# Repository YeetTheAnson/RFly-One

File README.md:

# RFly One

## Introduction
This project was inspired by [adsbee](https://github.com/PantsForBirds/adsbee) and [SoftRF](https://github.com/PantsForBirds/adsbee)!

This is the RFly One! This project was designed to be a fully offline general aviation proximity awareness system. The RFly One includes a custom ADS-B 1090MHz receiver frontend and support for FLARM AIR V7, OGNTP, FANET+ and more protocols, designed to keep pilots or enthusiasts aware of nearby manned or unmanned aerial vehicles without relying on an active internet connection.

The RFly One has a 2.4" TFT display to show nearby air traffic on an offline map (which can be loaded onto the SD card) or used as a flight insturment dashboard. It also has a BMI270 IMU and a MMC5983MA magnetometer to provide accurate heading, combined with an ATGM332D-5N31 GNSS module to show the current location on a map.

## Specifications

### Features
* **Awareness Protocols:** ADS-B, FLARM AIR V7, OGNTP, FANET+, RemoteID
* **Positioning:** GNSS, Gyro, Accelerometer, Magnetometer
* **Storage:** MicroSD Card (For offline maps and flight logging)
* **Charging:** 2A Max

### Hardware
* **Main Processor** ESP32-S3
* **ADS-B Decoder:** RP2040
* **Button/Power Control:** CH32V003
* **GNSS:** ATGM332D-5N31
* **IMU:** BMI270
* **Magnetometer:** MMC5983MA
* **LoRa Radio:** E80-900M2212S (LR2021)
* **Display:** 2.4" TFT

## Pinout
| Feature | Pin name | ESP32 Pin | Description |
|---|---|---|---|
| **LCD** | `LCD_MOSI` | `GPIO 42` | SPI MOSI |
| | `LCD_MISO` | `GPIO 39` | SPI MISO |
| | `LCD_SCK` | `GPIO 41` | SPI Clock |
| | `LCD_CS` | `GPIO 44` | SPI Chip Select |
| | `LCD_LED` | `GPIO 40` | Backlight Control |
| | `LCD_CMD` | `GPIO 43` | LCD Command |
| **IMU** | `SDA` | `GPIO 36` | I2C Data |
| | `SCL` | `GPIO 35` | I2C Clock |
| **SD Card** | `SDIO_DAT0` | `GPIO 9` | Data 0 |
| | `SDIO_DAT1` | `GPIO 8` | Data 1 |
| | `SDIO_DAT2` | `GPIO 12` | Data 2 |
| | `SDIO_DAT3` | `GPIO 13` | Data 3 |
| | `SDIO_CMD` | `GPIO 11` | SD Command |
| | `SDIO_CD` | `GPIO 7` | SD Detect |
| | `SDIO_CLK` | `GPIO 10` | SD Clock |
| **LoRa Radio** | `LORA_MOSI` | `GPIO 2` | SPI MOSI |
| | `LORA_MISO` | `GPIO 1` | SPI MISO |
| | `LORA_SCK` | `GPIO 4` | SPI Clock |
| | `LORA_CE` | `GPIO 5` | SPI Chip Enable |
| | `LORA_BUSY` | `GPIO 16` | Radio Busy |
| **GNSS Module** | `GNSS_TX` | `GPIO 15` | UART RX |
| | `GNSS_RX` | `GPIO 14` | UART TX |
| | `PPS` | `GPIO 17` | GNSS Time |
| **Button/Power Control** | `CH32_TX` | `GPIO 21` | UART RX |
| | `CH32_RX` | `GPIO 18` | UART TX |
| | `BATT_ADC` | `GPIO 6` | ADC1 |
| **ADSB Decoder** | `RP_TX` | `GPIO 47` | UART RX |
| | `RP_RX` | `GPIO 48` | UART TX |
| | `ADSB_CLK` | `GPIO 34` | Extracted Clock From ADSB Signal |

----

## Hardware Overview

----

## Firmware

### Building the RP2040 Firmware
1. Clone [this repository](https://github.com/YeetTheAnson/RFly-One) and enter the directory `cd RFly-One`
2. Open the `/firmware/source/rp2040.ino` file in ArduinoIDE
3. Paste `https://github.com/earlephilhower/arduino-pico/releases/download/global/package_rp2040_index.json` into `File > Preferences > Additional boards manager URLs`
4. Go to boards manager and install `Raspberry Pi Pico/RP2040/RP2350` by Earle F. Philhower, III
5. Click the upload button or `Sketch > Export Compiled Binary`

### Building the CH32V003 Firmware
1. Clone [this repository](https://github.com/YeetTheAnson/RFly-One) and enter the directory `cd RFly-One`
2. Open the `/firmware/source/ch32v003.ino` file in ArduinoIDE
3. Paste `https://alexandermandera.github.io/arduino-wch32v003/package_ch32v003_index.json` into `File > Preferences > Additional boards manager URLs`
4. Go to boards manager and install `WCH Boards` by Alexander Mandera
5. Click the upload button or `Sketch > Export Compiled Binary`

### Building the ESP32S3 Firmware
1. Clone [this repository](https://github.com/YeetTheAnson/RFly-One) and enter the directory `cd RFly-One`
2. Open the `/firmware/source/esp32.ino` file in ArduinoIDE
3. Paste `https://espressif.github.io/arduino-esp32/package_esp32_index.json` into `File > Preferences > Additional boards manager URLs`
4. Go to boards manager and install `ESP32` by Espressif
5. Click the upload button or `Sketch > Export Compiled Binary`

----

## Assembly

### Component List
* **Shell:**
    - [TopCase1.stl](https://github.com/YeetTheAnson/RFly-One/tree/main/production/3dPrint/TopCase1.stl)
    - [TopCase2.stl](https://github.com/YeetTheAnson/RFly-One/tree/main/production/3dPrint/TopCase2.stl)
    - [BottomCase.stl](https://github.com/YeetTheAnson/RFly-One/tree/main/production/3dPrint/BottomCase.stl)
* **PCB:**
    - [RFlyOne.zip](https://github.com/YeetTheAnson/RFly-One/tree/main/production/PCB/RFlyOne.zip)  
* **Fasteners:** 4x M2 10mm Self Tapping Screws
* **Battery:** Generic 500mAh LiPo battery (Size of battery is your choice)
* **SD Card:** Generic micro SD Card
* **Antennae:**
    - 2x 2400MHz FPC Antenna
    - 1x 1090MHz FPC Antenna
    - 1x 900MHz FPC Antenna
    - 1x Active GPS Ceramic Antenna

### Assembly Instructions
1. Slide the 3d printed parts `TopCase1.stl` and `TopCase2.stl` into place underneath the TFT LCD board.

2. Attach the battery using double sided adhesives and solder the battery cable onto the dedicated pad. Then connect the 2.4GHz WiFi antenna, 2.4GHz LoRa antenna, 1090MHz ADSB antenna and 900MHz LoRa antenna, and secure the FPC antennae to `BottomCase.stl` using double sided adhesives.

3. Feed the GNSS antenana cable through the `BottomCase.stl` cutout and glue the antenna to the bottom case. Then connect the GNSS antenna connector to the PCB and close the case.

4. Secure the case using 4x M2 10mm Self Tapping Screws

----

## Bill of Material

| Category | Item Name | Description | Link | Vendor | Quantity | Total Price (USD) |
|---|---|---|---|---|---:|---:|
| PCB Components | CL10A106MA8NRNC | 10uF 0603 capacitor | [link](https://www.lcsc.com/product-detail/C96446.html) | LCSC | 20 | 1.52 |
| PCB Components | AO3401A | P channel MOSFET | [link](https://www.lcsc.com/product-detail/C15127.html) | LCSC | 5 | 0.51 |
| PCB Components | GRM1555C1H101JA01D | 100pF 0402 capacitor | [link](https://www.lcsc.com/product-detail/C77177.html) | LCSC | 50 | 0.55 |
| PCB Components | GJM1555C1H3R0BB01D | 3pF 0402 capacitor | [link](https://www.lcsc.com/product-detail/C88891.html) | LCSC | 50 | 0.86 |
| PCB Components | CC0402JRNPO9BN201 | 200pF 0402 capacitor | [link](https://www.lcsc.com/product-detail/C325462.html) | LCSC | 50 | 0.45 |
| PCB Components | CC0402KRX7R9BB102 | 1nF 0402 capacitor | [link](https://www.lcsc.com/product-detail/C106205.html) | LCSC | 100 | 0.23 |
| PCB Components | CC0402JRNPO9BN150 | 15pF 0402 capacitor | [link](https://www.lcsc.com/product-detail/C106997.html) | LCSC | 100 | 0.20 |
| PCB Components | CL21A226MOQNNNE | 22uF 0805 capacitor | [link](https://www.lcsc.com/product-detail/C98190.html) | LCSC | 10 | 1.06 |
| PCB Components | RClamp3361P-ES | 0.25pF DFN1006 TVS diode | [link](https://www.lcsc.com/product-detail/C22464622.html) | LCSC | 5 | 0.60 |
| PCB Components | 0402L020/6SR | 200mA 0402 PTC Fuse | [link](https://www.lcsc.com/product-detail/C53280164.html) | LCSC | 10 | 0.71 |
| PCB Components | LQW15CN77NJ10D | 77nH 0402 inductor | [link](https://www.lcsc.com/product-detail/C668466.html) | LCSC | 10 | 0.88 |
| PCB Components | LQG15HS10NJ02D | 10nH 0402 inductor | [link](https://www.lcsc.com/product-detail/C77103.html) | LCSC | 50 | 0.93 |
| PCB Components | RC0402FR-0727RL | 27R 0402 resistor | [link](https://www.lcsc.com/product-detail/C138021.html) | LCSC | 100 | 0.40 |
| PCB Components | RC0402FR-0745K3L | 45.3k 0402 resistor | [link](https://www.lcsc.com/product-detail/C137977.html) | LCSC | 100 | 0.17 |
| PCB Components | FRC0402F2701TS | 2.7k 0402 resistor | [link](https://www.lcsc.com/product-detail/C2909332.html) | LCSC | 100 | 0.19 |
| PCB Components | FRC0402F1600TS | 160R 0402 resistor | [link](https://www.lcsc.com/product-detail/C2933075.html) | LCSC | 100 | 0.18 |
| PCB Components | FRC0402F3300TS | 330R 0402 resistor | [link](https://www.lcsc.com/product-detail/C2930002.html) | LCSC | 100 | 0.22 |
| PCB Components | FRC0402F7322TS | 73.2k 0402 resistor | [link](https://www.lcsc.com/product-detail/C2998163.html) | LCSC | 100 | 0.19 |
| PCB Components | 0402WGF7501TCE | 7.5k 0402 resistor | [link](https://www.lcsc.com/product-detail/C25918.html) | LCSC | 100 | 0.22 |
| PCB Components | ABM8-272-T3 | 12MHz 10pF 3225 crystal | [link](https://www.lcsc.com/product-detail/C20625731.html) | LCSC | 1 | 0.63 |
| PCB Components | ATGM332D-5N31 | GNSS module | [link](https://www.lcsc.com/product-detail/C128659.html) | LCSC | 1 | 3.58 |
| PCB Components | BMI270 | IMU | [link](https://www.lcsc.com/product-detail/C2836813.html) | LCSC | 2 | 5.75 |
| PCB Components | BQ25606RGER | Battery charge controller | [link](https://www.lcsc.com/product-detail/C374063.html) | LCSC | 1 | 1.64 |
| PCB Components | MMC5983MA | Magnetometer | [link](https://www.lcsc.com/product-detail/C404329.html) | LCSC | 1 | 2.28 |
| PCB Components | RT9193-33GB | 3.3V LDO regulator | [link](https://www.lcsc.com/product-detail/C15651.html) | LCSC | 5 | 0.69 |
| PCB Components | TA0970A | 1090MHz SAW filter | [link](https://www.lcsc.com/product-detail/C7115531.html) | LCSC | 2 | 3.09 |
| PCB Components | TLV3201AIDBVR | Comparator | [link](https://www.lcsc.com/product-detail/C105188.html) | LCSC | 1 | 0.98 |
| PCB Components | TPS61023DRLR | Boost converter | [link](https://www.lcsc.com/product-detail/C919459.html) | LCSC | 5 | 1.24 |
| PCB Components | TPS7A0230PDBVR | ULC 3V LDO regulator | [link](https://www.lcsc.com/product-detail/C3747031.html) | LCSC | 1 | 0.45 |
| PCB Components | TQP3M9036 | LNA | [link](https://www.lcsc.com/product-detail/C920261.html) | LCSC | 2 | 6.29 |
| PCB Components | TXU0202DTTR | Logic level translator | [link](https://www.lcsc.com/product-detail/C18197534.html) | LCSC | 2 | 1.62 |
| PCB Components | W25Q128JVSIQ | 128Mb 16MB NOR flash | [link](https://www.lcsc.com/product-detail/C97521.html) | LCSC | 1 | 2.58 |
| PCB Components | ESP32-S3-MINI-1U-N4R2 | Main processor | [link](https://www.lcsc.com/product-detail/C22356044.html) | LCSC | 1 | 4.61 |
| PCB Components | RP2040 | ADSB decoder coprocessor | [link](https://www.lcsc.com/product-detail/C2040.html) | LCSC | 1 | 1.00 |
| PCB Components | LCSC Shipping | 4PX | - | LCSC | 1 | 4.71 |
| PCB | PCB | 4 layer bare PCB | - | JLCPCB | 1 | 8.00 |
| PCB | JLCPCB Shipping | E-POST | - | JLCPCB | 1 | 5.78 |
| PCB Components | E80-900M2213S | LR2021 LoRA module | [link](https://www.aliexpress.com/item/1005012863308600.html) | AliExpress | 1 | 8.69 |
| PCB Components | AD8313ARMZ | RF logarithmic power detector | [link](https://www.aliexpress.com/item/1005009749065916.html) | AliExpress | 1 | 3.31 |
| PCB Components | AliExpress Shipping | AliExpress Shipping | - | AliExpress | 1 | 5.79 |
| Parts | 2.4" TFT LCD | 2.4" TFT LCD | [link](https://shopee.com.my/TFT-Display-0.96-1.3-1.44-1.77-1.8-2.4-2.8-inch-IPS-7P-SPI-HD-65K-TFT-Full-Color-LCD-Module-ST7735-Drive-IC-80*160-For-Arduino-i.299149454.21474104300) | Shopee | 1 | 4.35 |
| Parts | UWB 700-2700MHz antenna large | For 1090MHz ADSB receiver | [link](https://shopee.com.my/Gsm-3G-4G-LTE-5G-nb-iot-iot-Module-Signal-Enhancement-FPC-PCB-Built-in-Patch-Antenna-i.419312080.27871596372) | Shopee | 1 | 0.70 |
| Parts | UWB 700-2700MHz antenna small | For 900MHz LoRa transceiver | [link](https://shopee.com.my/Gsm-3G-4G-LTE-5G-nb-iot-iot-Module-Signal-Enhancement-FPC-PCB-Built-in-Patch-Antenna-i.419312080.27871596373) | Shopee | 1 | 0.65 |
| Parts | 2.4GHz antenna | For ESP32 WiFi/BT and LoRa | [link](https://shopee.com.my/2.4g-5g-5.8g-Dual-Band-Antenna-Built-in-FPC-Soft-Board-Antenna-wifi-Bluetooth-PCB-Patch-ipex-Antenna-i.419312080.27171149912) | Shopee | 2 | 0.95 |
| Parts | Shopee Shipping | SPX Express | - | Shopee | 2 | 2.60 |

- **PCB Components Total:** $69.00
- **PCB Total:** $13.78
- **Parts Total:** $9.25
### **Grand Total:** $92.03

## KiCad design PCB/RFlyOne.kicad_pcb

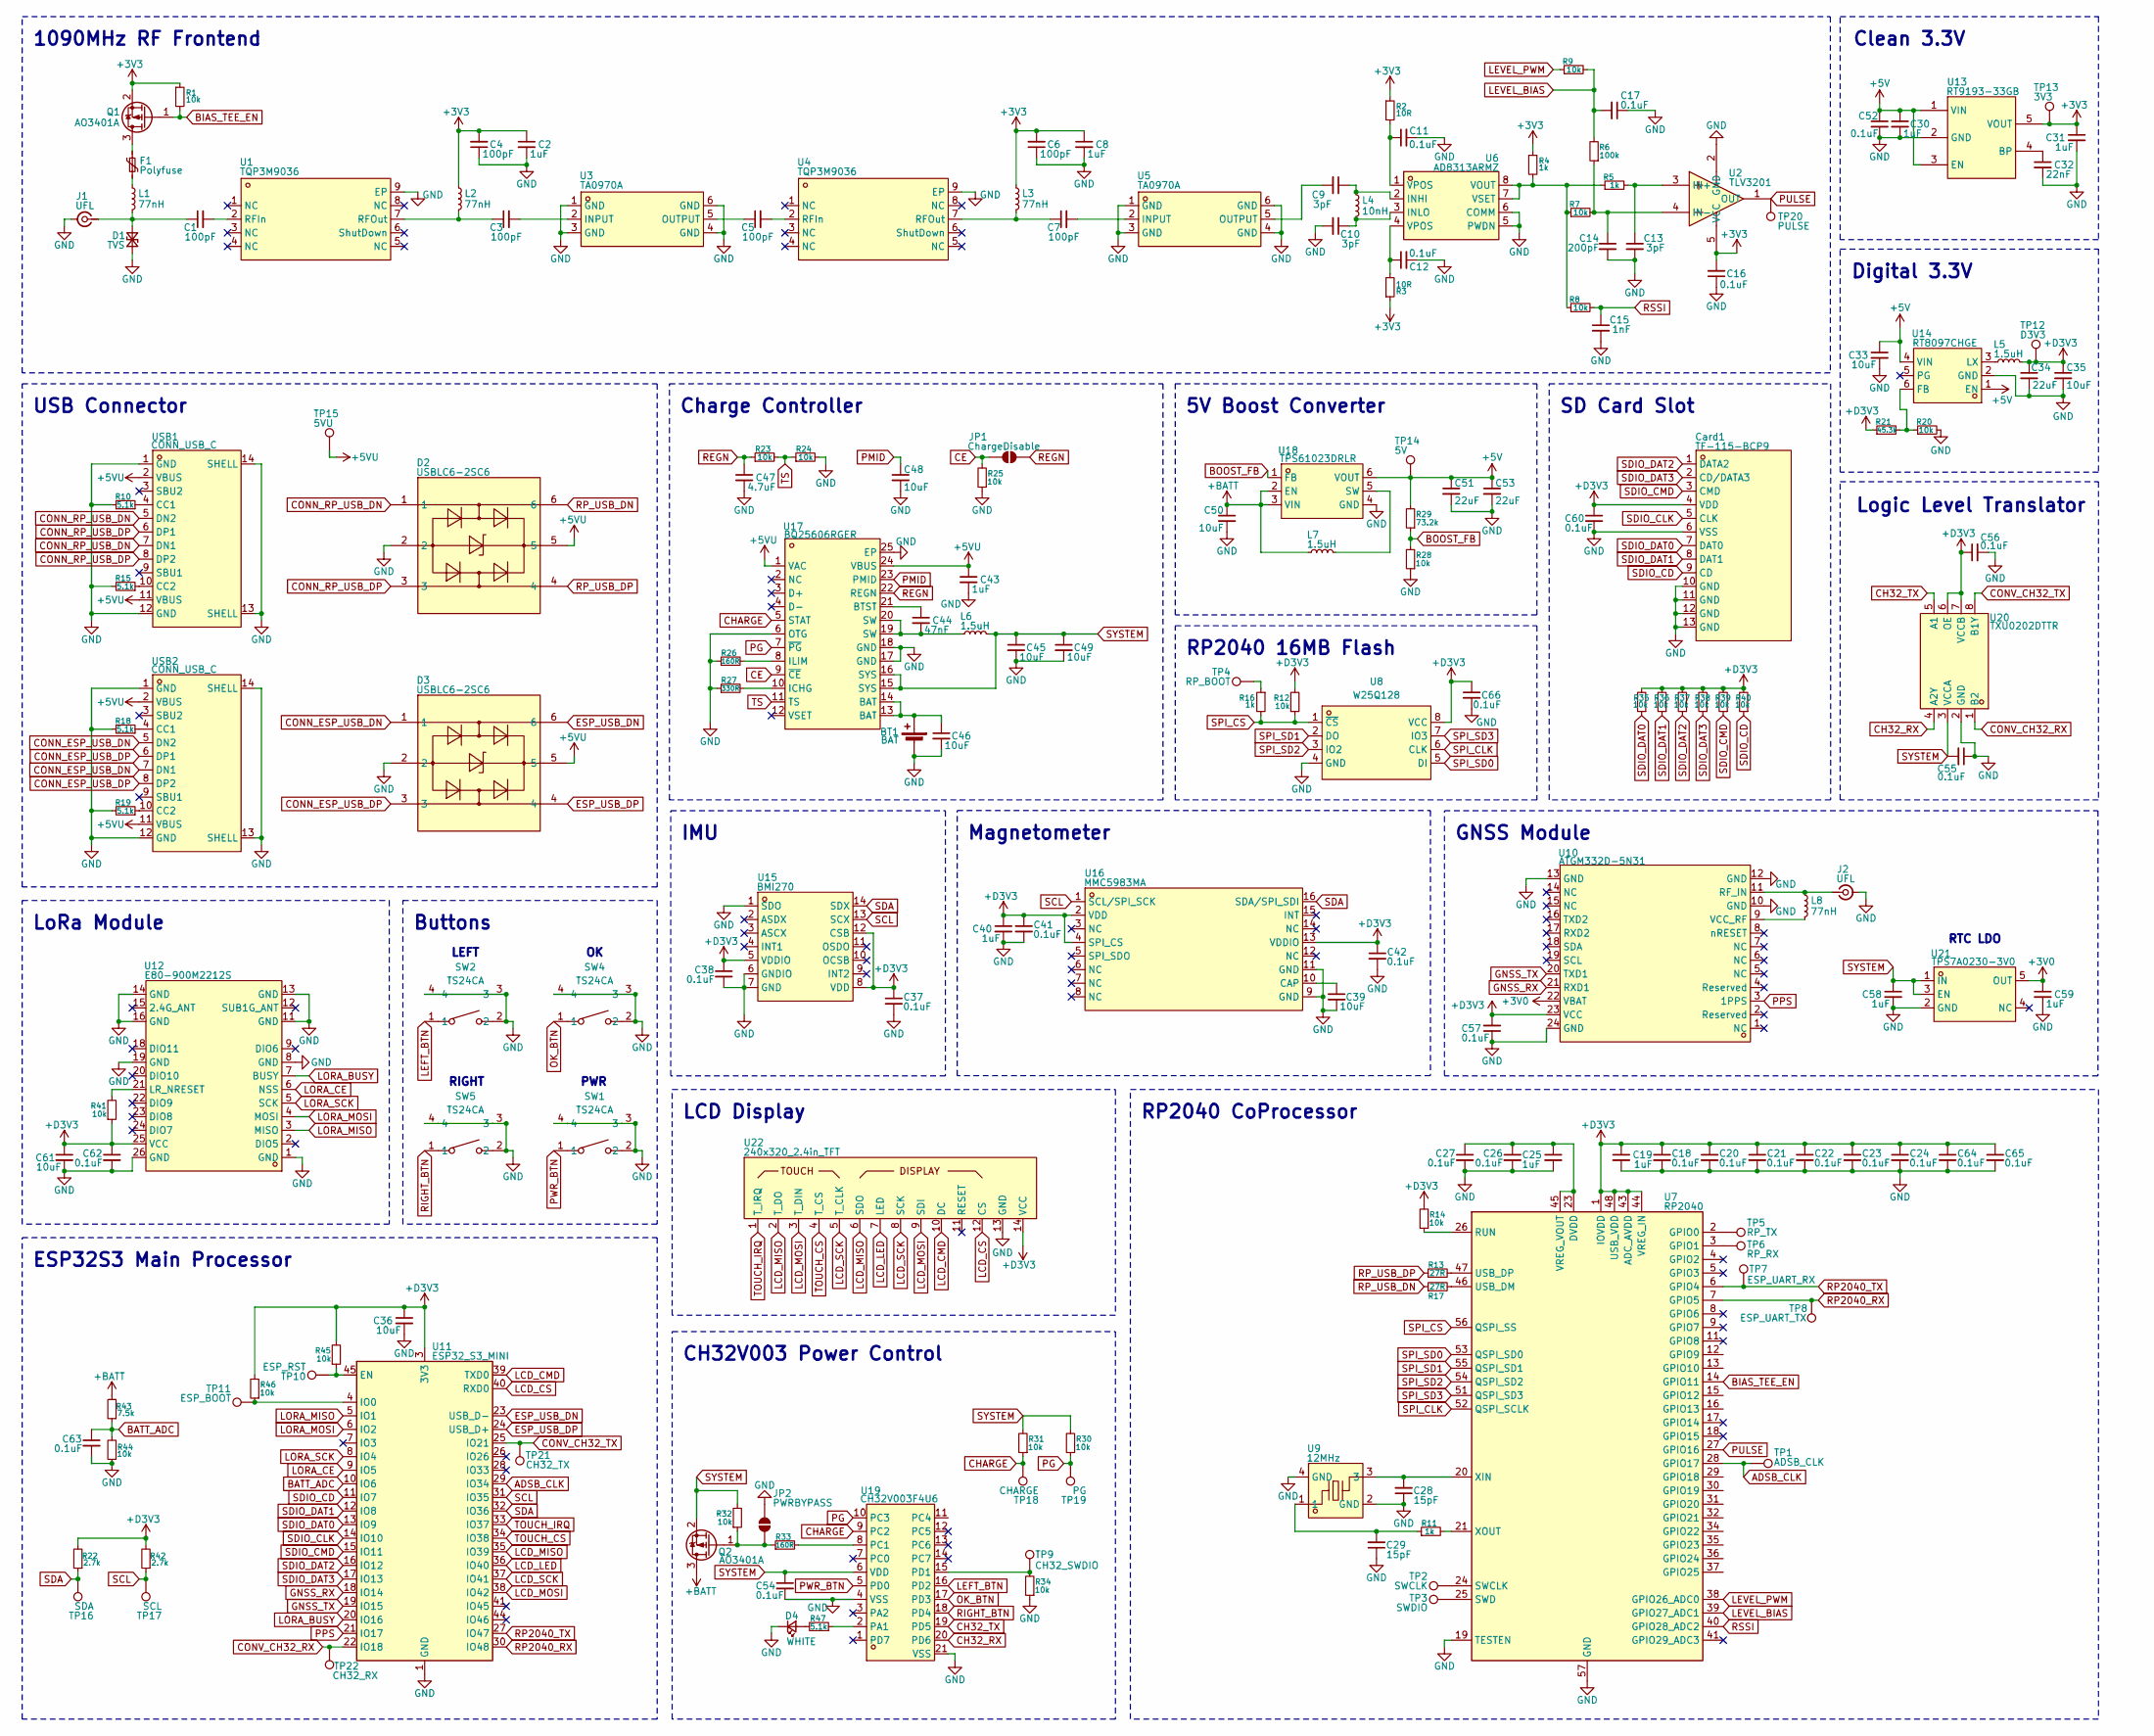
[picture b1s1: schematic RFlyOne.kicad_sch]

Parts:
BT1: BAT; Battery
C1, C3, C4, C5, C6, C7: 100pF; C_0402_1005Metric; LCSC Part C77177
C2, C8, C19, C25, C30, C31, C40, C43, C58, C59: 1uF; C_0402_1005Metric; LCSC Part C52923
C9, C10, C13: 3pF; C_0402_1005Metric; LCSC Part C88891
C11, C12, C16, C17, C18, C20, C21, C22, C23, C24, C26, C27, C37, C38, C41, C42, C52, C54, C55, C56, C57, C60, C62, C63, C64, C65, C66: 0.1uF; C_0402_1005Metric; LCSC Part C307331
C14: 200pF; C_0402_1005Metric; LCSC Part C325462
C15: 1nF; C_0402_1005Metric; LCSC Part C106205
C28, C29: 15pF; C_0402_1005Metric; LCSC Part C106997
C32: 22nF; C_0402_1005Metric; LCSC Part C1532
C33, C35, C36, C39, C45, C46, C48, C49, C50, C61: 10uF; C_0603_1608Metric; LCSC Part C96446
C34: 22uF; C_0603_1608Metric; LCSC Part C59461
C44: 47nF; C_0402_1005Metric; LCSC Part C272875
C47: 4.7uF; C_0402_1005Metric; LCSC Part C23733
C51, C53: 22uF; C_0805_2012Metric; LCSC Part C98190
Card1: TF-115-BCP9; TF-SMD_TF-115-BCP9; MPN TF-115-BCP9; LCSC Part C720505
D1: TVS; DFN-2_L1.0-W0.6-P0.65-BI; LCSC Part C22464622
D2, D3: USBLC6-2SC6; SOT-23-6_L2.9-W1.6-P0.95-LS2.8-BL; MPN USBLC6-2SC6; LCSC Part C7519
D4: WHITE; LED-SMD_L1.6-W1.1-R-RD_WHITE; LCSC Part C46635136
F1: Polyfuse; R_0402_1005Metric; LCSC Part C53280164
J1, J2: UFL; LCSC Part C5137195
JP1: ChargeDisable; SolderJumper-2_P1.3mm_Open_RoundedPad1.0x1.5mm
JP2: PWRBYPASS; SolderJumper-2_P1.3mm_Open_RoundedPad1.0x1.5mm
L1, L2, L3, L8: 77nH; L_0402_1005Metric; LCSC Part C668466
L4: 10nH; L_0402_1005Metric; LCSC Part C77103
L5, L6, L7: 1.5uH; L_Changjiang_FTC201610S; LCSC Part C5832343
Q1, Q2: AO3401A; SOT-23; LCSC Part C15127
R1, R7, R8, R9, R12, R14, R20, R23, R24, R25, R28, R30, R31, R32, R34, R35, R36, R37, R38, R39, R40, R41, R44, R45, R46: 10k; R_0402_1005Metric; LCSC Part C25744
R2, R3: 10R; R_0402_1005Metric; LCSC Part C25077
R4, R5, R11, R16: 1k; R_0402_1005Metric; LCSC Part C11702
R6: 100k; R_0402_1005Metric; LCSC Part C25741
R10, R15, R18, R19, R47: 5.1k; R_0402_1005Metric; LCSC Part C25905
R13, R17: 27R; R_0402_1005Metric; LCSC Part C138021
R21: 45.3k; R_0402_1005Metric; LCSC Part C137977
R22, R42: 2.7k; R_0402_1005Metric; LCSC Part C2909332
R26, R33: 160R; R_0402_1005Metric; LCSC Part C2933075
R27: 330R; R_0402_1005Metric; LCSC Part C2930002
R29: 73.2k; R_0402_1005Metric; LCSC Part C2998163
R43: 7.5k; R_0402_1005Metric; LCSC Part C25918
SW1, SW2, SW4, SW5: TS24CA; SW-SMD_2P-TS24CA; MPN TS24CA; LCSC Part C393942
TP1: ADSB_CLK; TestPoint
TP2: SWCLK; TestPoint
TP3: SWDIO; TestPoint
TP4: RP_BOOT; TestPoint
TP5: RP_TX; TestPoint
TP6: RP_RX; TestPoint
TP7: ESP_UART_RX; TestPoint
TP8: ESP_UART_TX; TestPoint
TP9: CH32_SWDIO; TestPoint
TP10: ESP_RST; TestPoint
TP11: ESP_BOOT; TestPoint
TP12: D3V3; TestPoint
TP13: 3V3; TestPoint
TP14: 5V; TestPoint
TP15: 5VU; TestPoint
TP16: SDA; TestPoint
TP17: SCL; TestPoint
TP18: CHARGE; TestPoint
TP19: PG; TestPoint
TP20: PULSE; TestPoint
TP21: CH32_TX; TestPoint
TP22: CH32_RX; TestPoint
U1, U4: TQP3M9036; DFN-8_L2.0-W2.0-P0.50-BL-EP; MPN TQP3M9036; LCSC Part C920261
U2: TLV3201; SOT-23-5_L3.0-W1.7-P0.95-LS2.8-BR; MPN TLV3201AIDBVR; LCSC Part C105188
U3, U5: TA0970A; FILTER-SMD_6P-L3.8-W3.8-BL; MPN TA0970A; LCSC Part C7115531
U6: AD8313ARMZ; MSOP-8_L3.0-W3.0-P0.65-LS4.9-BL; MPN AD8313ARMZ; LCSC Part C578690
U7: RP2040; QFN-56-1EP_7x7mm_P0.4mm_EP3.2x3.2mm; LCSC Part C2040
U8: W25Q128; SOIC-8_L5.3-W5.3-P1.27-LS8.0-BL; MPN W25Q128JVSIQ; LCSC Part C97521
U9: 12MHz; CRYSTAL-SMD_4P-L3.2-W2.5-BL; MPN ABM8-272-T3; LCSC Part C20625731
U10: ATGM332D-5N31; GSM-SMD_ATGM332D-5N31; MPN ATGM332D-5N31; LCSC Part C128659
U11: ESP32_S3_MINI; ESP32-S2-MINI-1U; LCSC Part C22356044
U12: E80-900M2212S; WIRELM-SMD_E80-900M2212S; MPN E80-900M2212S; LCSC Part C55338904
U13: RT9193-33GB; SOT-23-5_L3.0-W1.7-P0.95-LS2.8-BL; MPN RT9193-33GB; LCSC Part C15651
U14: RT8097CHGE; SOT-23-6_L2.9-W1.6-P0.95-LS2.8-BL; MPN RT8097CHGE; LCSC Part C3031673
U15: BMI270; LGA-14_L3.0-W2.5-P0.50-BR; MPN BMI270; LCSC Part C2836813
U16: MMC5983MA; LGA-16_L3.0-W3.0-P0.50-BL_SQ; MPN MMC5983MA; LCSC Part C404329
U17: BQ25606RGER; VQFN-24_L4.0-W4.0-P0.50-TL-EP2.8; MPN BQ25606RGER; LCSC Part C374063
U18: TPS61023DRLR; SOT-563_L1.6-W1.2-P0.50-LS1.6-BR; MPN TPS61023DRLR; LCSC Part C919459
U19: CH32V003F4U6; QFN-20_L3.0-W3.0-P0.40-TL-EP1.7; MPN CH32V003F4U6; LCSC Part C5299908
U20: TXU0202DTTR; XSON-8_L2.0-W1.0-P0.50-BL; MPN TXU0202DTTR; LCSC Part C18197534
U21: TPS7A0230-3V0; SOT-23-5_L2.9-W1.6-P0.95-LS2.8-BR; MPN TPS7A0230PDBVR; LCSC Part C3747031
U22: 240x320_2.4in_TFT; 2.4TFT
USB1, USB2: CONN_USB_C; USB-C-SMD_TYPE-C-6PIN-2MD-073; LCSC Part C2765186

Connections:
+3V0: C59.1, U10.22 (VBAT), U21.5 (OUT)
+3V3: C2.1, C4.2, C6.2, C8.1, C16.2, C31.1, L2.1, L3.1, Q1.2 (S), R1.1, R2.1, R3.1, R4.1, TP13.1, U2.5 (VCC), U13.5 (VOUT)
+5V: C30.1, C33.1, C51.1, C52.1, C53.1, R29.2, TP14.1, U13.1 (VIN), U13.3 (EN), U14.1 (EN), U14.4 (VIN), U18.6 (VOUT)
+5VU: C43.1, D2.5, D3.5, TP15.1, U17.1 (VAC), U17.24 (VBUS), USB1.2 (VBUS), USB1.11 (VBUS), USB2.2 (VBUS), USB2.11 (VBUS)
+BATT: C50.1, L7.1, Q2.3 (D), R43.2, U18.2 (EN), U18.3 (VIN)
+D3V3: C18.1, C19.1, C20.1, C21.1, C22.1, C23.1, C24.1, C34.1, C35.1, C36.1, C37.1, C38.1, C40.1, C41.1, C42.1, C56.1, C57.2, C60.1, C61.1, C62.1, C64.1, C65.1, C66.1, Card1.4 (VDD), L5.2, R12.2, R14.2, R21.1, R22.2, R35.2, R36.2, R37.2, R38.2, R39.2, R40.2, R41.1, R42.2, R45.2, R46.2, TP12.1, U7.1 (IOVDD), U7.10 (IOVDD), U7.22 (IOVDD), U7.33 (IOVDD), U7.42 (IOVDD), U7.43 (ADC_AVDD), U7.44 (VREG_IN), U7.48 (USB_VDD), U7.49 (IOVDD), U8.8 (VCC), U10.23 (VCC), U11.3 (3V3), U12.25 (VCC), U15.5 (VDDIO), U15.8 (VDD), U15.12 (CSB), U16.2 (VDD), U16.4 (SPI_CS), U16.13 (VDDIO), U20.6 (OE), U20.7 (VCCB), U22.14 (VCC)
ADSB_CLK: TP1.1, U7.28 (GPIO17), U11.29 (IO34)
BATT_ADC: C63.1, R43.1, R44.2, U11.10 (IO6)
BIAS_TEE_EN: Q1.1 (G), R1.2, U7.14 (GPIO11)
BOOST_FB: R28.2, R29.1, U18.1 (FB)
CE: JP1.1 (A), R25.2, U17.9 (~CE)
CH32_RX: U19.20 (PD6), U20.4 (A2Y)
CH32_TX: U19.19 (PD5), U20.5 (A1)
CHARGE: R31.1, TP18.1, U17.5 (STAT), U19.9 (PC2)
CONN_ESP_USB_DN: D3.1, USB2.5 (DN2), USB2.7 (DN1)
CONN_ESP_USB_DP: D3.3, USB2.6 (DP1), USB2.8 (DP2)
CONN_RP_USB_DN: D2.1, USB1.5 (DN2), USB1.7 (DN1)
CONN_RP_USB_DP: D2.3, USB1.6 (DP1), USB1.8 (DP2)
CONV_CH32_RX: TP22.1, U11.22 (IO18), U20.1 (B2)
CONV_CH32_TX: TP21.1, U11.25 (IO21), U20.8 (B1Y)
ESP_USB_DN: D3.6, U11.23 (USB_D-)
ESP_USB_DP: D3.4, U11.24 (USB_D+)
GND: BT1.2 (-), C2.2, C4.1, C6.1, C8.2, C10.2, C11.2, C12.2, C13.2, C14.2, C15.2, C16.1, C17.1, C18.2, C19.2, C20.2, C21.2, C22.2, C23.2, C24.2, C25.2, C26.2, C27.2, C28.1, C29.1, C30.2, C31.2, C32.2, C33.2, C34.2, C35.2, C36.2, C37.2, C38.2, C39.2, C40.2, C41.2, C42.2, C43.2, C45.2, C46.2, C47.2, C48.2, C49.2, C50.2, C51.2, C52.2, C53.2, C54.2, C55.1, C56.2, C57.1, C58.2, C59.2, C60.2, C61.2, C62.2, C63.2, C64.2, C65.2, C66.2, Card1.6 (VSS), Card1.10 (GND), Card1.11 (GND), Card1.12 (GND), Card1.13 (GND), D1.1 (A1), D2.2, D3.2, D4.1 (K), J1.2 (Ext), J2.2 (Ext), JP2.2 (B), R10.2, R15.2, R18.2, R19.2, R20.2, R24.2, R25.1, R26.1, R27.1, R28.1, R34.1, R44.1, SW1.2, SW1.3, SW1.4, SW2.2, SW2.3, SW2.4, SW4.2, SW4.3, SW4.4, SW5.2, SW5.3, SW5.4, U1.9 (EP), U2.2 (GND), U3.1 (GND), U3.3 (GND), U3.4 (GND), U3.6 (GND), U4.9 (EP), U5.1 (GND), U5.3 (GND), U5.4 (GND), U5.6 (GND), U6.5 (PWDN), U6.6 (COMM), U7.19 (TESTEN), U7.57 (GND), U8.4 (GND), U9.2 (GND), U9.4 (GND), U10.10 (GND), U10.12 (GND), U10.13 (GND), U10.24 (GND), U11.1 (GND), U11.2 (GND), U11.42 (GND), U11.43 (GND), U11.46 (GND), U11.47 (GND), U11.48 (GND), U11.49 (GND), U11.50 (GND), U11.51 (GND), U11.52 (GND), U11.53 (GND), U11.54 (GND), U11.55 (GND), U11.56 (GND), U11.57 (GND), U11.58 (GND), U11.59 (GND), U11.60 (GND), U11.61 (GND), U11.62 (GND), U11.63 (GND), U11.64 (GND), U11.65 (GND), U12.1 (GND), U12.8 (GND), U12.11 (GND), U12.13 (GND), U12.14 (GND), U12.16 (GND), U12.19 (GND), U12.26 (GND), U13.2 (GND), U14.2 (GND), U15.1 (SDO), U15.6 (GNDIO), U15.7 (GND), U16.9 (GND), U16.11 (GND), U17.6 (OTG), U17.17 (GND), U17.18 (GND), U17.25 (EP), U18.4 (GND), U19.4 (VSS), U19.21 (VSS), U20.2 (GND), U21.2 (GND), U22.13 (GND), USB1.1 (GND), USB1.12 (GND), USB1.13 (SHELL), USB1.14 (SHELL), USB2.1 (GND), USB2.12 (GND), USB2.13 (SHELL), USB2.14 (SHELL)
GNSS_RX: U10.21 (RXD1), U11.18 (IO14)
GNSS_TX: U10.20 (TXD1), U11.19 (IO15)
LCD_CMD: U11.39 (TXD0), U22.10 (DC)
LCD_CS: U11.40 (RXD0), U22.12 (CS)
LCD_LED: U11.36 (IO40), U22.7 (LED)
LCD_MISO: U11.35 (IO39), U22.2 (T_DO), U22.6 (SDO)
LCD_MOSI: U11.38 (IO42), U22.3 (T_DIN), U22.9 (SDI)
LCD_SCK: U11.37 (IO41), U22.5 (T_CLK), U22.8 (SCK)
LEFT_BTN: SW2.1, U19.16 (PD2)
LEVEL_BIAS: C17.2, R6.2, R9.2, U7.39 (GPIO27_ADC1)
LEVEL_PWM: R9.1, U7.38 (GPIO26_ADC0)
LORA_BUSY: U11.20 (IO16), U12.7 (BUSY)
LORA_CE: U11.9 (IO5), U12.6 (NSS)
LORA_MISO: U11.5 (IO1), U12.3 (MISO)
LORA_MOSI: U11.6 (IO2), U12.4 (MOSI)
LORA_SCK: U11.8 (IO4), U12.5 (SCK)
unnamed: BT1.1 (+), C46.1, U17.13 (BAT), U17.14 (BAT)
unnamed: C11.1, R2.2, U6.1 (VPOS)
unnamed: C12.1, R3.2, U6.4 (VPOS)
unnamed: C29.2, R11.1, U9.1
unnamed: C44.2, L6.1, U17.19 (SW), U17.20 (SW)
unnamed: C1.1, D1.2 (A2), J1.1 (In), L1.2
unnamed: D4.2 (A), R47.2
unnamed: F1.2, L1.1
unnamed: J2.1 (In), L8.1, U10.11 (RF_IN)
unnamed: JP2.1 (A), Q2.1 (G), R32.1, R33.1
unnamed: F1.1, Q1.3 (D)
unnamed: R16.1, TP4.1
unnamed: C1.2, U1.2 (RFIn)
unnamed: C3.1, L2.2, U1.7 (RFOut)
unnamed: C13.1, R5.2, U2.3 (IN+)
unnamed: C14.1, R6.1, R7.2, U2.4 (IN-)
unnamed: C3.2, U3.2 (INPUT)
unnamed: C5.1, U3.5 (OUTPUT)
unnamed: C5.2, U4.2 (RFIn)
unnamed: C7.1, L3.2, U4.7 (RFOut)
unnamed: C7.2, U5.2 (INPUT)
unnamed: C9.2, U5.5 (OUTPUT)
unnamed: C9.1, L4.1, U6.2 (INHI)
unnamed: C10.1, L4.2, U6.3 (INLO)
unnamed: R4.2, R5.1, R7.1, R8.1, U6.7 (VSET), U6.8 (VOUT)
unnamed: TP5.1, U7.2 (GPIO0)
unnamed: TP6.1, U7.3 (GPIO1)
unnamed: R14.1, U7.26 (RUN)
unnamed: TP2.1, U7.24 (SWCLK)
unnamed: TP3.1, U7.25 (SWD)
unnamed: R17.2, U7.46 (USB_DM)
unnamed: R13.2, U7.47 (USB_DP)
unnamed: C25.1, C26.1, C27.1, U7.23 (DVDD), U7.45 (VREG_VOUT), U7.50 (DVDD)
unnamed: C28.2, U7.20 (XIN), U9.3
unnamed: R11.2, U7.21 (XOUT)
unnamed: L8.2, U10.9 (VCC_RF)
unnamed: R45.1, TP10.1, U11.45 (EN)
unnamed: R46.1, TP11.1, U11.4 (IO0)
unnamed: R41.2, U12.21 (LR_NRESET)
unnamed: C32.1, U13.4 (BP)
unnamed: R20.1, R21.2, U14.6 (FB)
unnamed: L5.1, U14.3 (LX)
unnamed: C39.1, U16.10 (CAP)
unnamed: C44.1, U17.21 (BTST)
unnamed: R27.2, U17.10 (ICHG)
unnamed: R26.2, U17.8 (ILIM)
unnamed: L7.2, U18.5 (SW)
unnamed: R47.1, U19.2 (PA1)
unnamed: R33.2, U19.8 (PC1)
unnamed: R34.2, TP9.1, U19.15 (PD1)
unnamed: R10.1, USB1.4 (CC1)
unnamed: R15.1, USB1.10 (CC2)
unnamed: R18.1, USB2.4 (CC1)
unnamed: R19.1, USB2.10 (CC2)
OK_BTN: SW4.1, U19.17 (PD3)
PG: R30.1, TP19.1, U17.7 (~PG), U19.10 (PC3)
PMID: C48.1, U17.23 (PMID)
PPS: U10.3 (1PPS), U11.21 (IO17)
PULSE: TP20.1, U2.1 (OUT), U7.27 (GPIO16)
PWR_BTN: SW1.1, U19.5 (PD0)
REGN: C47.1, JP1.2 (B), R23.1, U17.22 (REGN)
RIGHT_BTN: SW5.1, U19.18 (PD4)
RP2040_RX: TP8.1, U7.7 (GPIO5), U11.30 (IO48)
RP2040_TX: TP7.1, U7.6 (GPIO4), U11.27 (IO47)
RP_USB_DN: D2.6, R17.1
RP_USB_DP: D2.4, R13.1
RSSI: C15.1, R8.2, U7.40 (GPIO28_ADC2)
SCL: R42.1, TP17.1, U11.31 (IO35), U15.13 (SCX), U16.1 (SCL/SPI_SCK)
SDA: R22.1, TP16.1, U11.32 (IO36), U15.14 (SDX), U16.16 (SDA/SPI_SDI)
SDIO_CD: Card1.9 (CD), R40.1, U11.11 (IO7)
SDIO_CLK: Card1.5 (CLK), U11.14 (IO10)
SDIO_CMD: Card1.3 (CMD), R39.1, U11.15 (IO11)
SDIO_DAT0: Card1.7 (DAT0), R35.1, U11.13 (IO9)
SDIO_DAT1: Card1.8 (DAT1), R36.1, U11.12 (IO8)
SDIO_DAT2: Card1.1 (DATA2), R37.1, U11.16 (IO12)
SDIO_DAT3: Card1.2 (CD/DATA3), R38.1, U11.17 (IO13)
SPI_CLK: U7.52 (QSPI_SCLK), U8.6 (CLK)
SPI_CS: R12.1, R16.2, U7.56 (QSPI_SS), U8.1 (~CS)
SPI_SD0: U7.53 (QSPI_SD0), U8.5 (DI)
SPI_SD1: U7.55 (QSPI_SD1), U8.2 (DO)
SPI_SD2: U7.54 (QSPI_SD2), U8.3 (IO2)
SPI_SD3: U7.51 (QSPI_SD3), U8.7 (IO3)
SYSTEM: C45.1, C49.1, C54.1, C55.2, C58.1, L6.2, Q2.2 (S), R30.2, R31.2, R32.2, U17.15 (SYS), U17.16 (SYS), U19.6 (VDD), U20.3 (VCCA), U21.1 (IN), U21.3 (EN)
TOUCH_CS: U11.34 (IO38), U22.4 (T_CS)
TOUCH_IRQ: U11.33 (IO37), U22.1 (T_IRQ)
TS: R23.2, R24.1, U17.11 (TS)

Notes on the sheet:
1090MHz RF Frontend
Buttons
RP2040 16MB Flash
RIGHT
LCD Display
Digital 3.3V
RTC LDO
Logic Level Translator
Charge Controller
Clean 3.3V
GNSS Module
PWR
LEFT
Magnetometer
LoRa Module
SD Card Slot
USB Connector
IMU
RP2040 CoProcessor
ESP32S3 Main Processor
5V Boost Converter
CH32V003 Power Control

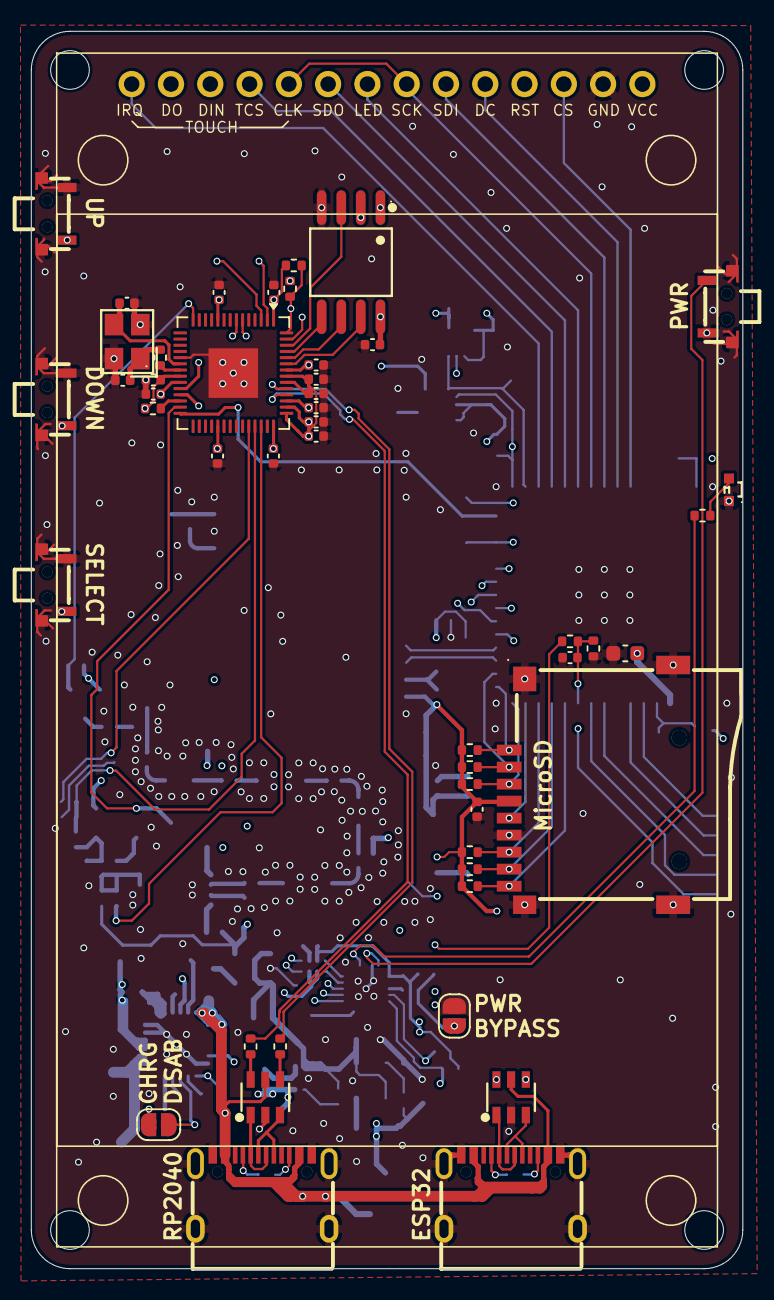
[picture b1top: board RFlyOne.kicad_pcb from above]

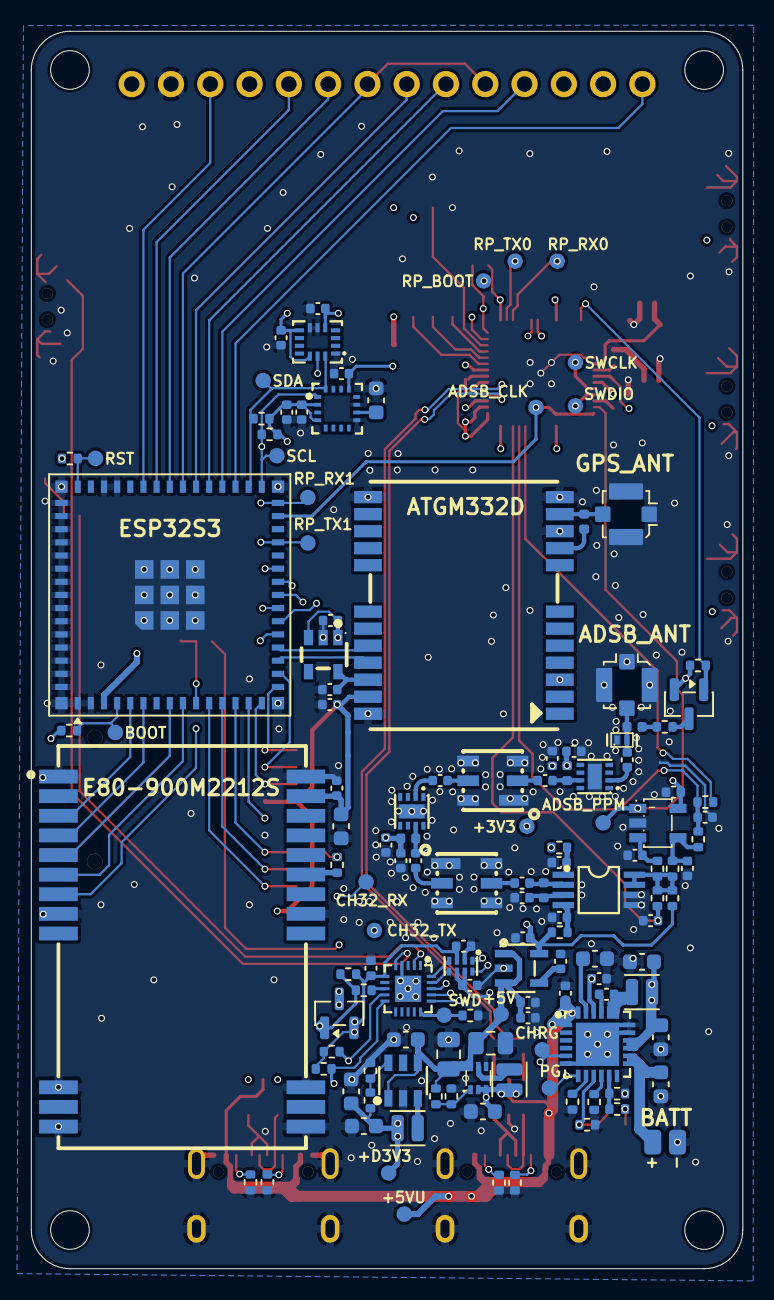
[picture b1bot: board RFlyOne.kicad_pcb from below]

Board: 4 copper layers, 46.0 x 80.0 mm, 184 parts (135 on the bottom side), 125 nets.

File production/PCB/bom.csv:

Designator,Footprint,Quantity,Value,LCSC Part #
"C1, C3, C4, C5, C6, C7",0402,6,100pF,C77177
"C10, C13, C9",0402,3,3pF,C88891
"C11, C12, C16, C17, C18, C20, C21, C22, C23, C24, C26, C27, C37, C38, C41, C42, C52, C54, C55, C56, C57, C60, C62, C63, C64, C65, C66",0402,27,0.1uF,C307331
C14,0402,1,200pF,C325462
C15,0402,1,1nF,C106205
"C19, C2, C25, C30, C31, C40, C43, C58, C59, C8",0402,10,1uF,C52923
"C28, C29",0402,2,15pF,C106997
C32,0402,1,22nF,C1532
"C33, C35, C36, C39, C45, C46, C48, C49, C50, C61",0603,10,10uF,C96446
C34,0603,1,22uF,C59461
C44,0402,1,47nF,C272875
C47,0402,1,4.7uF,C23733
"C51, C53",0805,2,22uF,C98190
CARD1,TF-SMD_TF-115-BCP9,1,TF-115-BCP9,C720505
D1,DFN-2_L1.0-W0.6-P0.65-BI,1,TVS,C22464622
"D2, D3",SOT-23-6_L2.9-W1.6-P0.95-LS2.8-BL,2,USBLC6-2SC6,C7519
D4,LED-SMD_L1.6-W1.1-R-RD_WHITE,1,WHITE,C46635136
F1,0402,1,Polyfuse,C53280164
"J1, J2",UFL,2,UFL,C5137195
"L1, L2, L3, L8",0402,4,77nH,C668466
L4,0402,1,10nH,C77103
"L5, L6, L7",L_Changjiang_FTC201610S,3,1.5uH,C5832343
"Q1, Q2",SOT-23,2,AO3401A,C15127
"R1, R12, R14, R20, R23, R24, R25, R28, R30, R31, R32, R34, R35, R36, R37, R38, R39, R40, R41, R44, R45, R46, R7, R8, R9",0402,25,10k,C25744
"R10, R15, R18, R19, R47",0402,5,5.1k,C25905
"R11, R16, R4, R5",0402,4,1k,C11702
"R13, R17",0402,2,27R,C138021
"R2, R3",0402,2,10R,C25077
R21,0402,1,45.3k,C137977
"R22, R42",0402,2,2.7k,C2909332
"R26, R33",0402,2,160R,C2933075
R27,0402,1,330R,C2930002
R29,0402,1,73.2k,C2998163
R43,0402,1,7.5k,C25918
R6,0402,1,100k,C25741
"SW1, SW2, SW4, SW5",SW-SMD_2P-TS24CA,4,TS24CA,C393942
"U1, U4",DFN-8_L2.0-W2.0-P0.50-BL-EP,2,TQP3M9036,C920261
U10,GSM-SMD_ATGM332D-5N31,1,ATGM332D-5N31,C128659
U11,ESP32-S2-MINI-1U,1,ESP32_S3_MINI,C22356044
U12,WIRELM-SMD_E80-900M2212S,1,E80-900M2212S,C55338904
U13,SOT-23-5_L3.0-W1.7-P0.95-LS2.8-BL,1,RT9193-33GB,C15651
U14,SOT-23-6_L2.9-W1.6-P0.95-LS2.8-BL,1,RT8097CHGE,C3031673
U15,LGA-14_L3.0-W2.5-P0.50-BR,1,BMI270,C2836813
U16,LGA-16_L3.0-W3.0-P0.50-BL_SQ,1,MMC5983MA,C404329
U17,VQFN-24_L4.0-W4.0-P0.50-TL-EP2.8,1,BQ25606RGER,C374063
U18,SOT-563_L1.6-W1.2-P0.50-LS1.6-BR,1,TPS61023DRLR,C919459
U19,QFN-20_L3.0-W3.0-P0.40-TL-EP1.7,1,CH32V003F4U6,C5299908
U2,SOT-23-5_L3.0-W1.7-P0.95-LS2.8-BR,1,TLV3201,C105188
U20,XSON-8_L2.0-W1.0-P0.50-BL,1,TXU0202DTTR,C18197534
U21,SOT-23-5_L2.9-W1.6-P0.95-LS2.8-BR,1,TPS7A0230-3V0,C3747031
"U3, U5",FILTER-SMD_6P-L3.8-W3.8-BL,2,TA0970A,C7115531
U6,MSOP-8_L3.0-W3.0-P0.65-LS4.9-BL,1,AD8313ARMZ,C578690
U7,QFN-56-1EP_7x7mm_P0.4mm_EP3.2x3.2mm,1,RP2040,C2040
U8,SOIC-8_L5.3-W5.3-P1.27-LS8.0-BL,1,W25Q128,C97521
U9,CRYSTAL-SMD_4P-L3.2-W2.5-BL,1,12MHz,C20625731
"USB1, USB2",USB-C-SMD_TYPE-C-6PIN-2MD-073,2,CONN_USB_C,C2765186

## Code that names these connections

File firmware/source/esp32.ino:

// Written with Gemini. Firmware time not counted.
#include <Arduino.h>
#include <SPI.h>
#include <Wire.h>
#include <Adafruit_GFX.h>
#include <Adafruit_ILI9341.h>
#include <Adafruit_BMI270.h>
#include <Adafruit_MMC5983.h>
#include <SD_MMC.h>
#include <RadioLib.h>

// --- Pin Definitions ---
// TFT LCD
#define LCD_MOSI   42
#define LCD_MISO   39
#define LCD_SCK    41
#define LCD_CMD    43
#define LCD_CS     44
#define LCD_LED    40

// I2C
#define I2C_SDA    36
#define I2C_SCL    35

// SDIO SD Card
#define SDIO_DAT0  9
#define SDIO_DAT1  8
#define SDIO_DAT2  12
#define SDIO_DAT3  13
#define SDIO_CMD   11
#define SDIO_CLK   10
#define SDIO_CD    7

// LoRa (LR2021 / LR1121)
#define LORA_BUSY  16
#define LORA_CE    5
#define LORA_SCK   4
#define LORA_MOSI  2
#define LORA_MISO  1

// GNSS
#define GNSS_TX_ESP_RX  15
#define GNSS_RX_ESP_TX  14
#define GNSS_PPS        17

// Coprocessors & ADSB
#define CH32_RX_PIN     21 // ESP RX
#define CH32_TX_PIN     18 // ESP TX
#define RP2040_RX_PIN   47 // ESP RX
#define RP2040_TX_PIN   48 // ESP TX
#define ADSB_CLK        34

// --- Peripherals & Objects ---
SPIClass tftSPI(FSPI);
Adafruit_ILI9341 tft = Adafruit_ILI9341(&tftSPI, LCD_CMD, LCD_CS, -1);

SPIClass loraSPI(HSPI);
LR1121 radio = new Module(LORA_CE, RADIOLIB_NC, RADIOLIB_NC, LORA_BUSY, loraSPI);

Adafruit_BMI270 bmi;
Adafruit_MMC5983MA mmc;

// Hardware UARTS (ESP32-S3 has 3: Serial0, Serial1, Serial2)
// Assumes USB CDC is enabled for the main `Serial` monitor.
HardwareSerial SerialRP(0);   
HardwareSerial SerialGNSS(1); 
HardwareSerial SerialCH(2);   

// --- Global State ---
bool sdOk = false;
bool loraOk = false;
bool bmiOk = false;
bool mmcOk = false;

volatile uint32_t adsb_pulse_count = 0;
uint32_t last_adsb_count = 0;
uint32_t last_update_ms = 0;

// ADSB Clock Interrupt
void IRAM_ATTR adsb_isr() {
    adsb_pulse_count++;
}

void setup() {
    Serial.begin(115200);

    // 1. Initialize TFT
    pinMode(LCD_LED, OUTPUT);
    digitalWrite(LCD_LED, HIGH); // Turn on backlight
    tftSPI.begin(LCD_SCK, LCD_MISO, LCD_MOSI, LCD_CS);
    tft.begin();
    tft.setRotation(3); // Landscape
    tft.fillScreen(ILI9341_BLACK);
    tft.setTextColor(ILI9341_WHITE, ILI9341_BLACK);
    tft.setTextSize(2);
    tft.setCursor(0, 0);
    tft.println("Initializing System...");

    // 2. Initialize I2C & Sensors
    Wire.begin(I2C_SDA, I2C_SCL);
    bmiOk = bmi.begin(0x68, &Wire);
    mmcOk = mmc.begin();

    // 3. Initialize SDIO SD Card
    pinMode(SDIO_CD, INPUT_PULLUP);
    SD_MMC.setPins(SDIO_CLK, SDIO_CMD, SDIO_DAT0, SDIO_DAT1, SDIO_DAT2, SDIO_DAT3);
    if (digitalRead(SDIO_CD) == LOW) { // Card Detected
        sdOk = SD_MMC.begin();
    }

    // 4. Initialize LoRa
    loraSPI.begin(LORA_SCK, LORA_MISO, LORA_MOSI, LORA_CE);
    int state = radio.begin();
    loraOk = (state == RADIOLIB_ERR_NONE);

    // 5. Initialize UARTS
    SerialGNSS.begin(9600, SERIAL_8N1, GNSS_TX_ESP_RX, GNSS_RX_ESP_TX);
    SerialCH.begin(115200, SERIAL_8N1, CH32_RX_PIN, CH32_TX_PIN);
    SerialRP.begin(115200, SERIAL_8N1, RP2040_RX_PIN, RP2040_TX_PIN);

    // 6. Initialize ADSB Clock Interrupt
    pinMode(ADSB_CLK, INPUT);
    attachInterrupt(digitalPinToInterrupt(ADSB_CLK), adsb_isr, RISING);
}

void loop() {
    uint32_t now = millis();
    
    // Update screen and run checks every 500ms
    if (now - last_update_ms >= 500) {
        last_update_ms = now;
        
        tft.setCursor(0, 0);

        // --- I2C Sensors ---
        if (bmiOk) {
            sensors_event_t accel, gyro, temp;
            bmi.getEvent(&accel, &gyro, &temp);
            tft.printf("BMI: X:%.1f Y:%.1f  \n", accel.acceleration.x, accel.acceleration.y);
        } else {
            tft.println("BMI270: FAIL       ");
        }

        if (mmcOk) {
            sensors_event_t magEvent;
            mmc.getEvent(&magEvent);
            tft.printf("MMC: X:%.0f Y:%.0f  \n", magEvent.magnetic.x, magEvent.magnetic.y);
        } else {
            tft.println("MMC5983: FAIL      ");
        }

        // --- SD Card ---
        tft.printf("SD Card: %s \n", (sdOk && digitalRead(SDIO_CD) == LOW) ? "OK      " : "NOT MNT ");

        // --- LoRa ---
        tft.printf("LR2021: %s \n", loraOk ? "OK      " : "FAIL    ");

        // --- ADSB Clock ---
        uint32_t current_count = adsb_pulse_count;
        uint32_t hz = (current_count - last_adsb_count) * 2; // *2 because loop is 500ms
        last_adsb_count = current_count;
        tft.printf("ADSB CLK: %lu Hz   \n", hz);

        // --- GNSS ---
        bool gnssData = false;
        while (SerialGNSS.available()) {
            SerialGNSS.read(); // Flush buffer
            gnssData = true;
        }
        tft.printf("GNSS UART: %s \n", gnssData ? "ACTIVE  " : "WAITING ");

        // --- CH32V003 Coprocessor ---
        SerialCH.print("C"); // Send test char
        delay(10); // Brief wait for loopback
        bool ch32Ok = false;
        while (SerialCH.available()) {
            if (SerialCH.read() == 'C') ch32Ok = true;
        }
        tft.printf("CH32 UART: %s \n", ch32Ok ? "LOOP OK " : "FAIL    ");

        // --- RP2040 Coprocessor ---
        SerialRP.print("R"); // Send test char
        delay(10);
        bool rpOk = false;
        while (SerialRP.available()) {
            if (SerialRP.read() == 'R') rpOk = true;
        }
        tft.printf("RP20 UART: %s \n", rpOk ? "LOOP OK " : "FAIL    ");
    }
}

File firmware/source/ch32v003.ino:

// Written with Gemini. Firmware time not counted.
// --- Pin Definitions ---
#define LED_PIN    PA1
#define MOSFET_PIN PC1

#define BTN_RIGHT  PD4
#define BTN_LEFT   PD2
#define BTN_OK     PD3
#define BTN_PWR    PD0

// --- Button Structure ---
struct Button {
  uint8_t pin;
  const char* name;
  bool state;
  bool lastReading;
  unsigned long lastDebounceTime;
};

// Initialize buttons (assuming default unpressed state is HIGH due to pull-ups)
Button buttons[4] = {
  {BTN_RIGHT, "RIGHT_BTN", HIGH, HIGH, 0},
  {BTN_LEFT,  "LEFT_BTN",  HIGH, HIGH, 0},
  {BTN_OK,    "OK_BTN",    HIGH, HIGH, 0},
  {BTN_PWR,   "PWR_BTN",   HIGH, HIGH, 0}
};

// --- State Variables ---
bool mosfetOn = false;        // MOSFET state track
bool ledState = LOW;          // LED state track
unsigned long lastBlink = 0;  // Blink timing

const unsigned long debounceDelay = 50; // 50ms debounce time

void setup() {
  // Initialize UART at 115200 baud (Defaults to PD5 TX, PD6 RX)
  Serial.begin(115200);

  // Initialize LED
  pinMode(LED_PIN, OUTPUT);

  // Initialize P-Channel MOSFET
  // PC1 goes LOW to turn on, so we initialize it to HIGH (OFF)
  pinMode(MOSFET_PIN, OUTPUT);
  digitalWrite(MOSFET_PIN, HIGH);

  // Initialize Buttons with internal pull-ups
  for (int i = 0; i < 4; i++) {
    pinMode(buttons[i].pin, INPUT_PULLUP);
    buttons[i].state = digitalRead(buttons[i].pin);
    buttons[i].lastReading = buttons[i].state;
  }
}

void loop() {
  unsigned long currentMillis = millis();

  // 1. Non-blocking LED Blink (Toggle every 500ms)
  if (currentMillis - lastBlink >= 500) {
    lastBlink = currentMillis;
    ledState = !ledState;
    digitalWrite(LED_PIN, ledState);
  }

  // 2. UART Message Relay (Echo RX to TX)
  while (Serial.available() > 0) {
    Serial.write(Serial.read());
  }

  // 3. Button Reading & Debouncing
  for (int i = 0; i < 4; i++) {
    bool reading = digitalRead(buttons[i].pin);

    // If the switch changed (due to noise or pressing)
    if (reading != buttons[i].lastReading) {
      buttons[i].lastDebounceTime = currentMillis;
    }

    // If the reading has been stable longer than the debounce delay
    if ((currentMillis - buttons[i].lastDebounceTime) > debounceDelay) {
      // If the actual button state has changed
      if (reading != buttons[i].state) {
        buttons[i].state = reading;

        // Send state change over UART
        Serial.print(buttons[i].name);
        Serial.print(" ");
        Serial.println(buttons[i].state); // 0 when pressed, 1 when released

        // 4. Special handling for PWR Button toggle logic
        // Check if this is the PWR button and it was just pressed (went LOW)
        if (buttons[i].pin == BTN_PWR && buttons[i].state == LOW) {
          mosfetOn = !mosfetOn;
          
          if (mosfetOn) {
            digitalWrite(MOSFET_PIN, LOW);  // Turn P-MOSFET ON
          } else {
            digitalWrite(MOSFET_PIN, HIGH); // Turn P-MOSFET OFF
          }
        }
      }
    }
    // Save the reading for the next loop comparison
    buttons[i].lastReading = reading;
  }
}
